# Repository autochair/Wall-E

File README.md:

View this project on [CADLAB.io](https://cadlab.io/node/973). 

# Wall-E

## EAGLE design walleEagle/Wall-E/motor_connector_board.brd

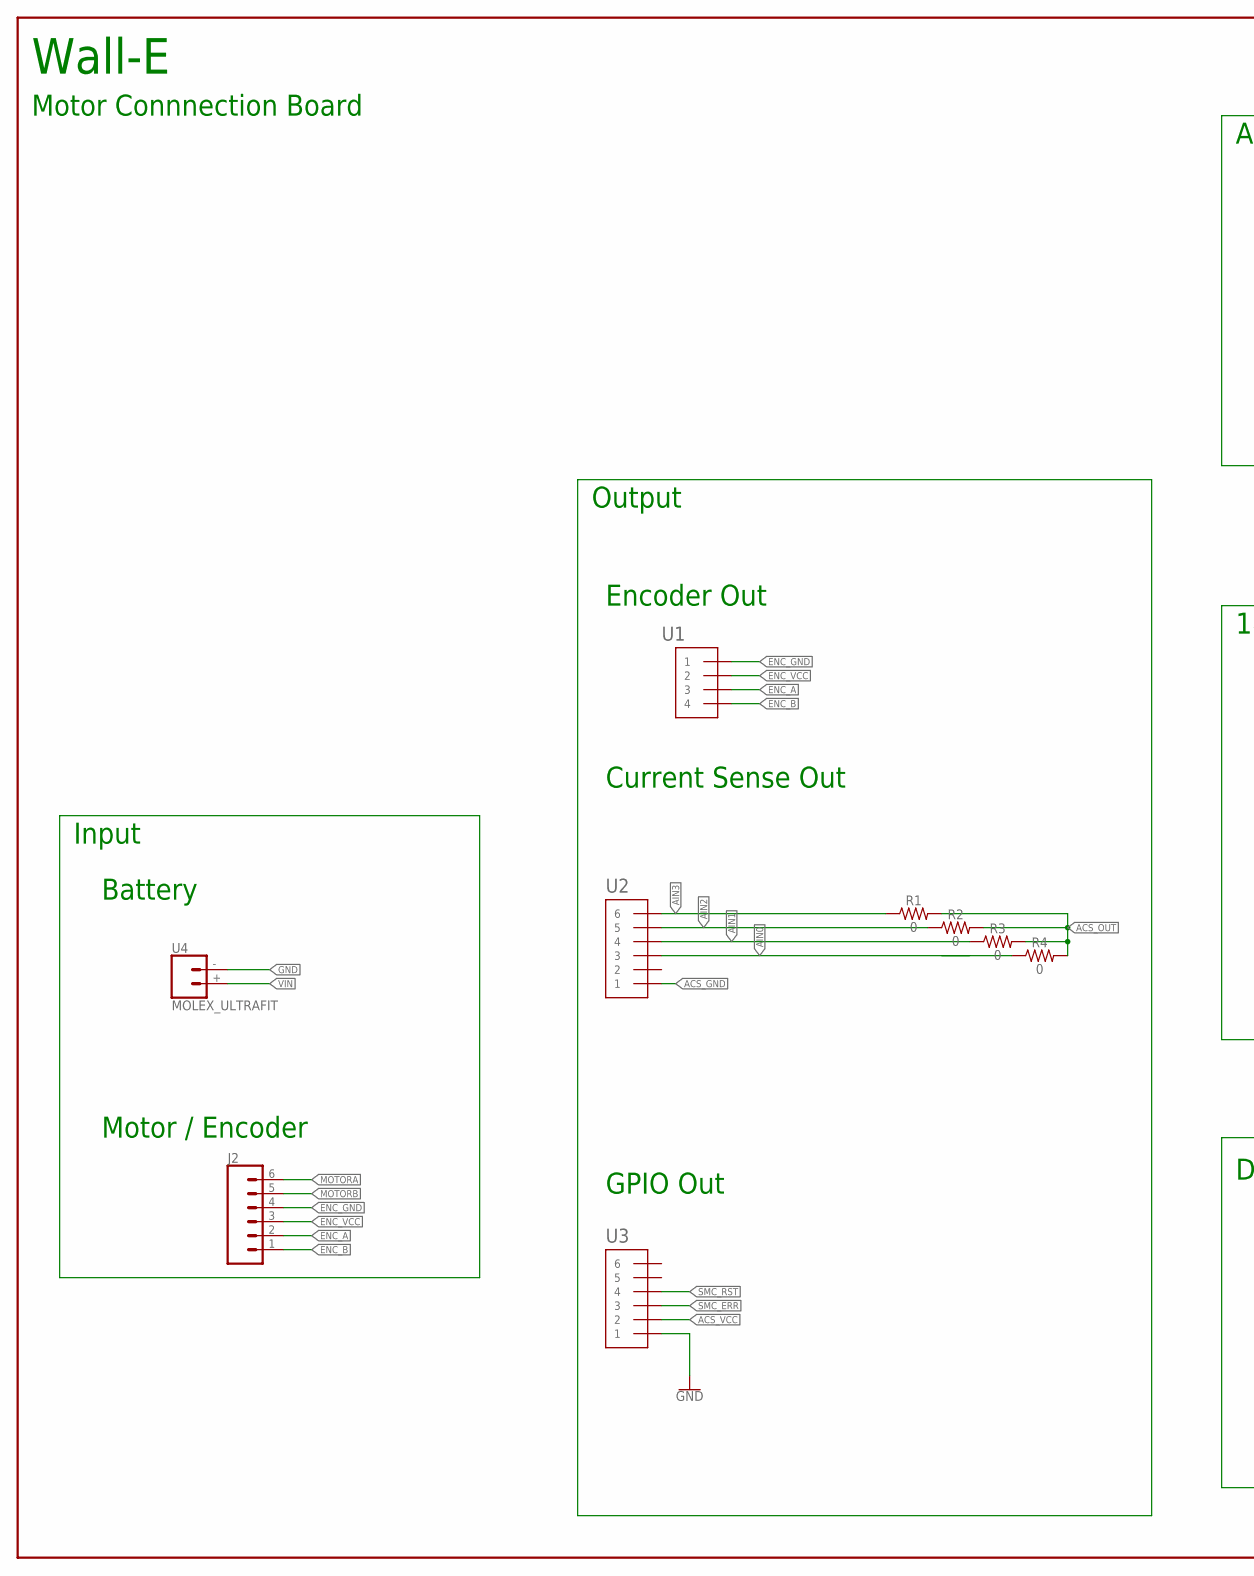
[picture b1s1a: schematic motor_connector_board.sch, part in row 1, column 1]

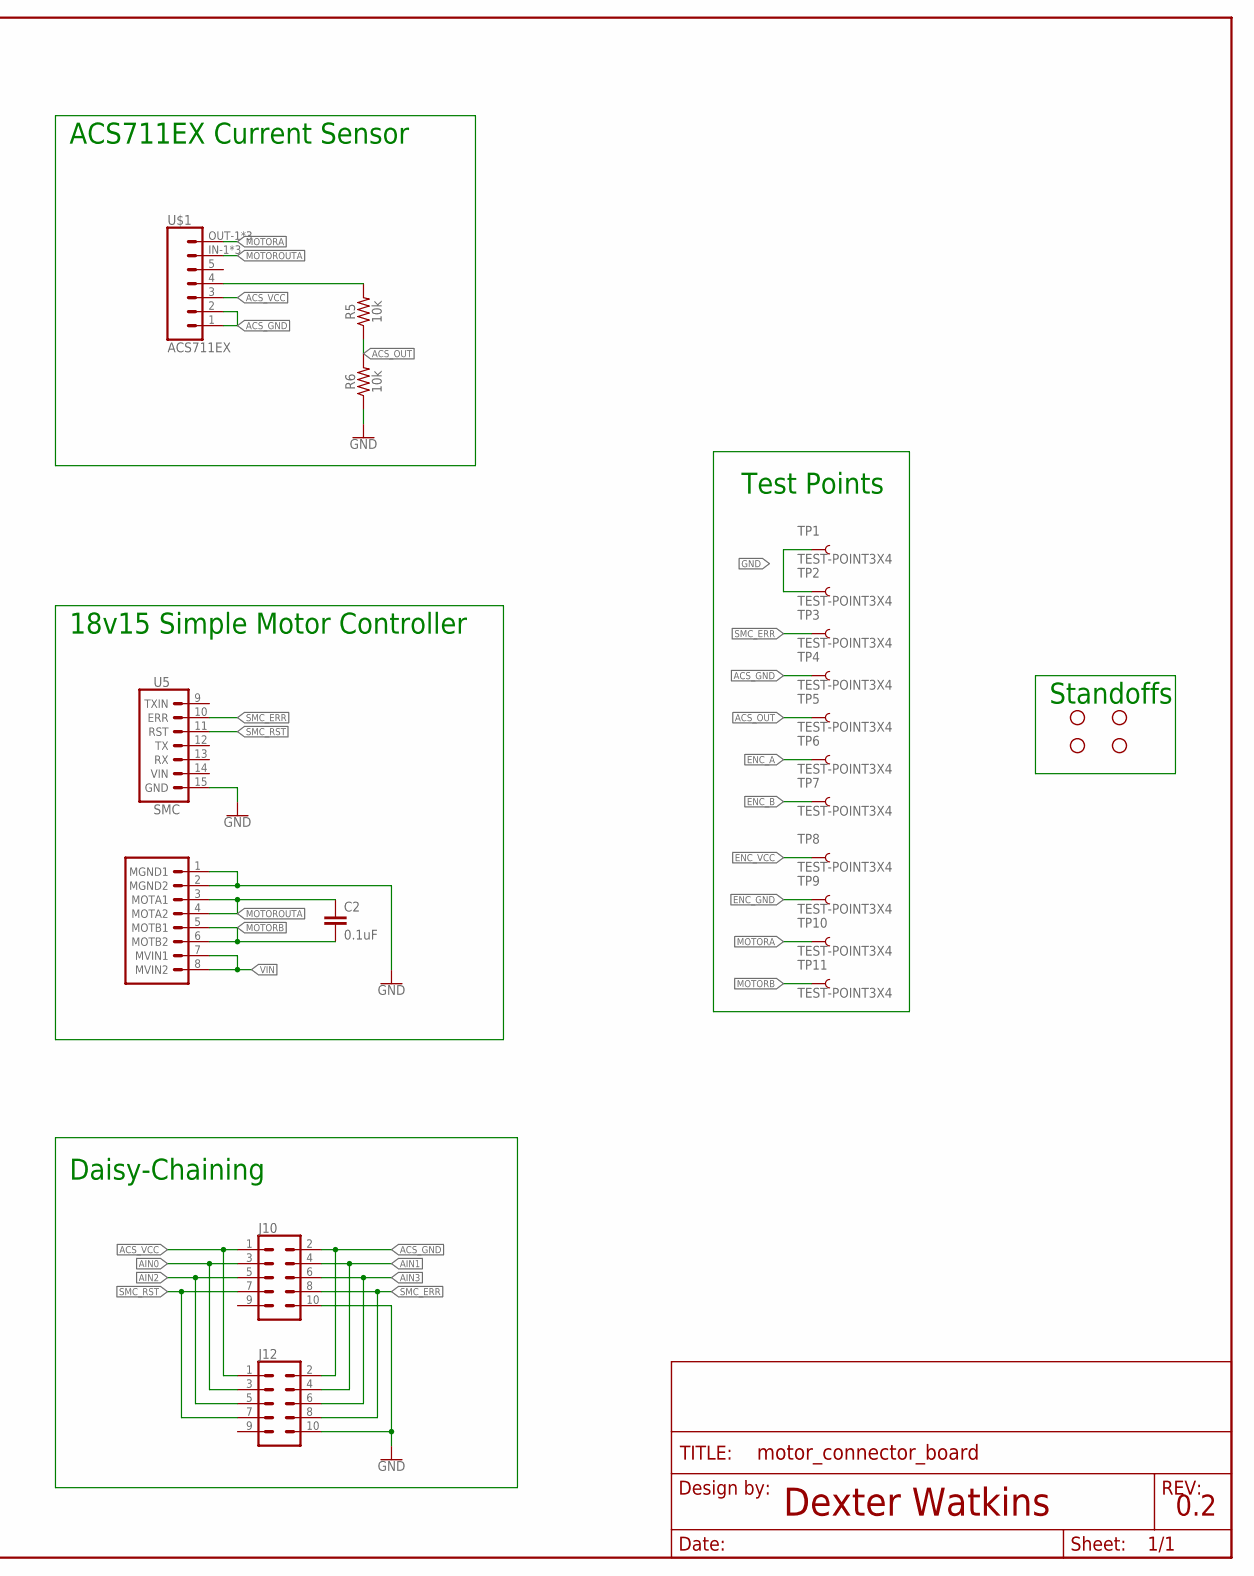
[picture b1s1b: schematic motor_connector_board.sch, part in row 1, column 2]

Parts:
C2: 0.1uF; 0603
FRAME1: FRAME-LEDGER; CREATIVE_COMMONS
H1, H2, H3, H4: STAND-OFF
J2: CONN_06LONGPADS; 1X06_LONGPADS
J10, J12: CONN_05X2SHD_LOCK; 2X5-SHROUDED_LOCK
R1, R2, R3, R4: 0; 0603
R5, R6: 10k; 0603
TP1, TP2, TP3, TP4, TP5, TP6, TP7, TP8, TP9, TP10, TP11: TEST-POINT3X4; PAD.03X.04
U1: JST_SH_4; JST_SH_4_SMD
U2, U3: JST_SH_6
U4: MOLEX_ULTRAFIT; MOLEX_ULTRAFIT-2CKT
U5: SMC
U$1: ACS711EX; ACS_CURRENT_SENSOR

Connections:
ACS_3.3OUT: R5.2, U$1.4
ACS_GND: J10.2, J12.2, TP4.P$1, U2.1, U$1.1, U$1.2
ACS_OUT: R1.2, R2.2, R3.2, R4.2, R5.1, R6.2, TP5.P$1
ACS_VCC: J10.1, J12.1, U3.2, U$1.3
AIN0: J10.3, J12.3, R4.1, U2.3
AIN1: J10.4, J12.4, R3.1, U2.4
AIN2: J10.5, J12.5, R2.1, U2.5
AIN3: J10.6, J12.6, R1.1, U2.6
ENC_A: J2.2, TP6.P$1, U1.3
ENC_B: J2.1, TP7.P$1, U1.4
ENC_GND: J2.4, TP9.P$1, U1.1
ENC_VCC: J2.3, TP8.P$1, U1.2
GND: J10.10, J12.10, R6.1, TP1.P$1, TP2.P$1, U3.1, U4.- (2), U5.1 (MGND1), U5.2 (MGND2), U5.15 (GND)
MOTORA: J2.6, TP10.P$1, U$1.OUT-1 (7), U$1.OUT-2 (7), U$1.OUT-3 (7)
MOTORB: C2.2, J2.5, TP11.P$1, U5.5 (MOTB1), U5.6 (MOTB2)
MOTOROUTA: C2.1, U5.3 (MOTA1), U5.4 (MOTA2), U$1.IN-1 (6), U$1.IN-2 (6), U$1.IN-3 (6)
SMC_ERR: J10.8, J12.8, TP3.P$1, U3.3, U5.10 (ERR)
SMC_RST: J10.7, J12.7, U3.4, U5.11 (RST)
VIN: U4.+ (1), U5.7 (MVIN1), U5.8 (MVIN2)

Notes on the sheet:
Dexter Watkins
0.2
Wall-E
Motor Connnection Board
Battery
Motor / Encoder
Encoder Out
Current Sense Out
18v15 Simple Motor Controller
ACS711EX Current Sensor
Input
Output
GPIO Out
Daisy-Chaining
Standoffs
Test Points

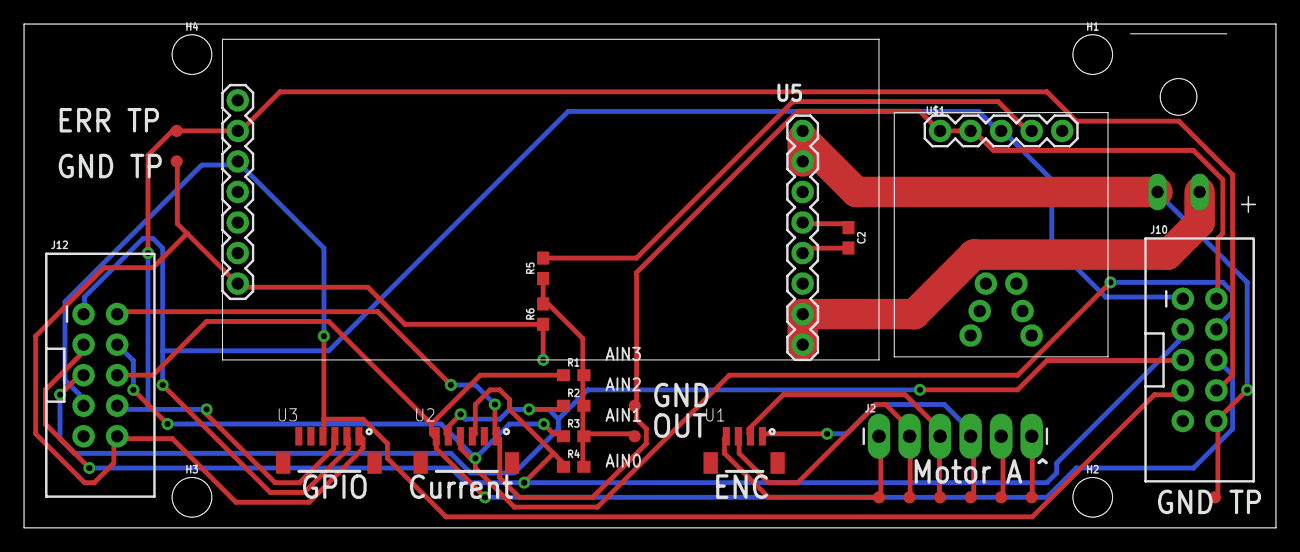
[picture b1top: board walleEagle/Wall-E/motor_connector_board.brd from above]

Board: 2 copper layers, 104.1 x 41.9 mm, 32 parts (0 on the bottom side), 19 nets.

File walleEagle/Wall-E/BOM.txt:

Partlist exported from C:/Users/dexte/Documents/repositories/Wall-E/Wall-E/motor_connector_board.sch at 12/27/2017 11:23 AM

Part   Value          Device                    Package             Description                                                                                                     PROD_ID    SF_ID     VALUE
C2     0.1uF          1.0NF/1000PF-0603-50V-10% 0603                1nF/1,000pF ceramic capacitors                                                                                  CAP-07886            1nF  
FRAME1 FRAME-LEDGER   FRAME-LEDGER              CREATIVE_COMMONS    Schematic Frame - Ledger                                                                                                                  
H1     STAND-OFF      STAND-OFF                 STAND-OFF           Stand Off                                                                                                                                 
H2     STAND-OFF      STAND-OFF                 STAND-OFF           Stand Off                                                                                                                                 
H3     STAND-OFF      STAND-OFF                 STAND-OFF           Stand Off                                                                                                                                 
H4     STAND-OFF      STAND-OFF                 STAND-OFF           Stand Off                                                                                                                                 
J2                    CONN_06LONGPADS           1X06_LONGPADS       Multi connection point. Often used as Generic Header-pin footprint for 0.1 inch spaced/style header connections                           
J10                   CONN_05X2SHD_LOCK         2X5-SHROUDED_LOCK   Multi connection point. Often used as Generic Header-pin footprint for 0.1 inch spaced/style header connections CONN-08671 PRT-08506      
J12                   CONN_05X2SHD_LOCK         2X5-SHROUDED_LOCK   Multi connection point. Often used as Generic Header-pin footprint for 0.1 inch spaced/style header connections CONN-08671 PRT-08506      
R1     0              0OHM-0603-1/10W-5%        0603                0O resistor                                                                                                     RES-08609            0    
R2     0              0OHM-0603-1/10W-5%        0603                0O resistor                                                                                                     RES-08609            0    
R3     0              0OHM-0603-1/10W-5%        0603                0O resistor                                                                                                     RES-08609            0    
R4     0              0OHM-0603-1/10W-5%        0603                0O resistor                                                                                                     RES-08609            0    
TP1    TEST-POINT3X4  TEST-POINT3X4             PAD.03X.04          SparkFun Test Points                                                                                                                      
TP2    TEST-POINT3X4  TEST-POINT3X4             PAD.03X.04          SparkFun Test Points                                                                                                                      
TP3    TEST-POINT3X4  TEST-POINT3X4             PAD.03X.04          SparkFun Test Points                                                                                                                      
TP4    TEST-POINT3X4  TEST-POINT3X4             PAD.03X.04          SparkFun Test Points                                                                                                                      
TP5    TEST-POINT3X4  TEST-POINT3X4             PAD.03X.04          SparkFun Test Points                                                                                                                      
TP6    TEST-POINT3X4  TEST-POINT3X4             PAD.03X.04          SparkFun Test Points                                                                                                                      
TP7    TEST-POINT3X4  TEST-POINT3X4             PAD.03X.04          SparkFun Test Points                                                                                                                      
TP8    TEST-POINT3X4  TEST-POINT3X4             PAD.03X.04          SparkFun Test Points                                                                                                                      
TP9    TEST-POINT3X4  TEST-POINT3X4             PAD.03X.04          SparkFun Test Points                                                                                                                      
TP10   TEST-POINT3X4  TEST-POINT3X4             PAD.03X.04          SparkFun Test Points                                                                                                                      
TP11   TEST-POINT3X4  TEST-POINT3X4             PAD.03X.04          SparkFun Test Points                                                                                                                      
U$1    ACS711EX       ACS711EX                  ACS_CURRENT_SENSOR                                                                                                                                            
U1     JST_SH_4       JST_SH_4                  JST_SH_4_SMD                                                                                                                                                  
U2     JST_SH_6       JST_SH_6                  JST_SH_6                                                                                                                                                      
U3     JST_SH_6       JST_SH_6                  JST_SH_6                                                                                                                                                      
U4     MOLEX_ULTRAFIT MOLEX_ULTRAFIT            MOLEX_ULTRAFIT-2CKT                                                                                                                                           
U5     SMC            SMC                       SMC

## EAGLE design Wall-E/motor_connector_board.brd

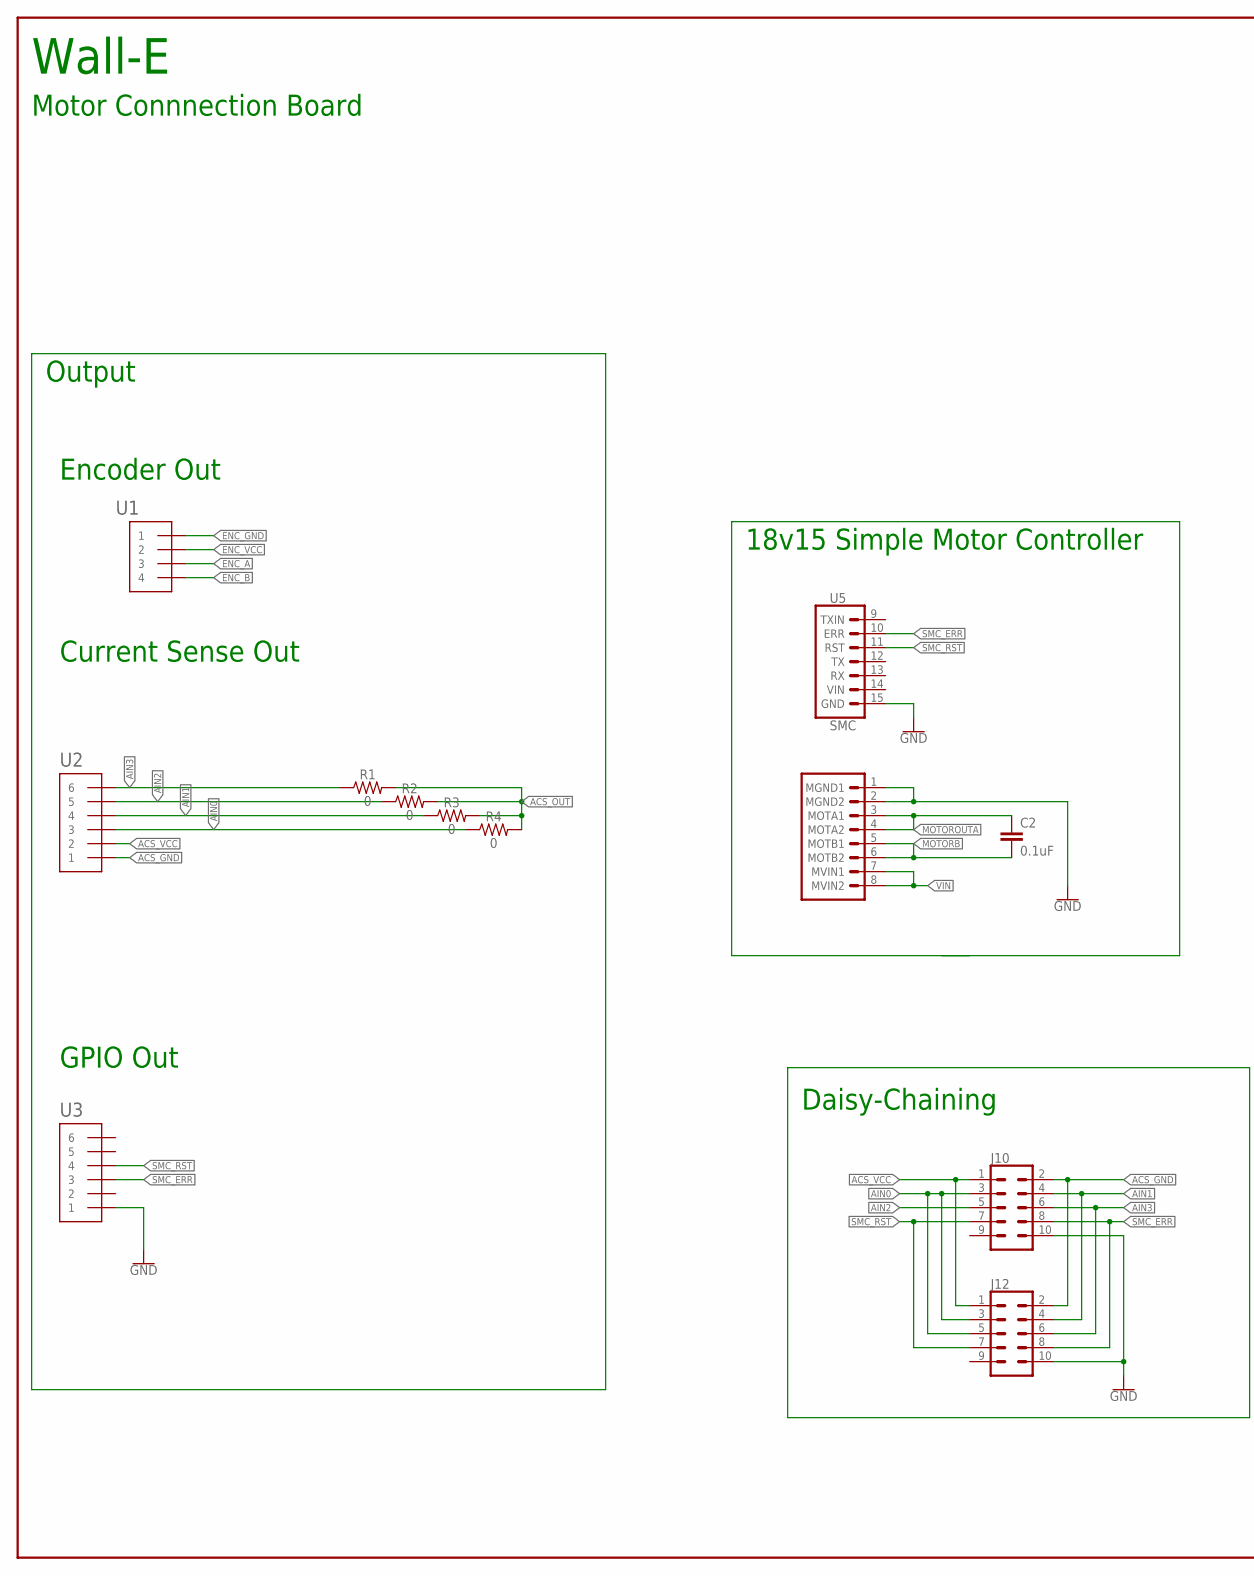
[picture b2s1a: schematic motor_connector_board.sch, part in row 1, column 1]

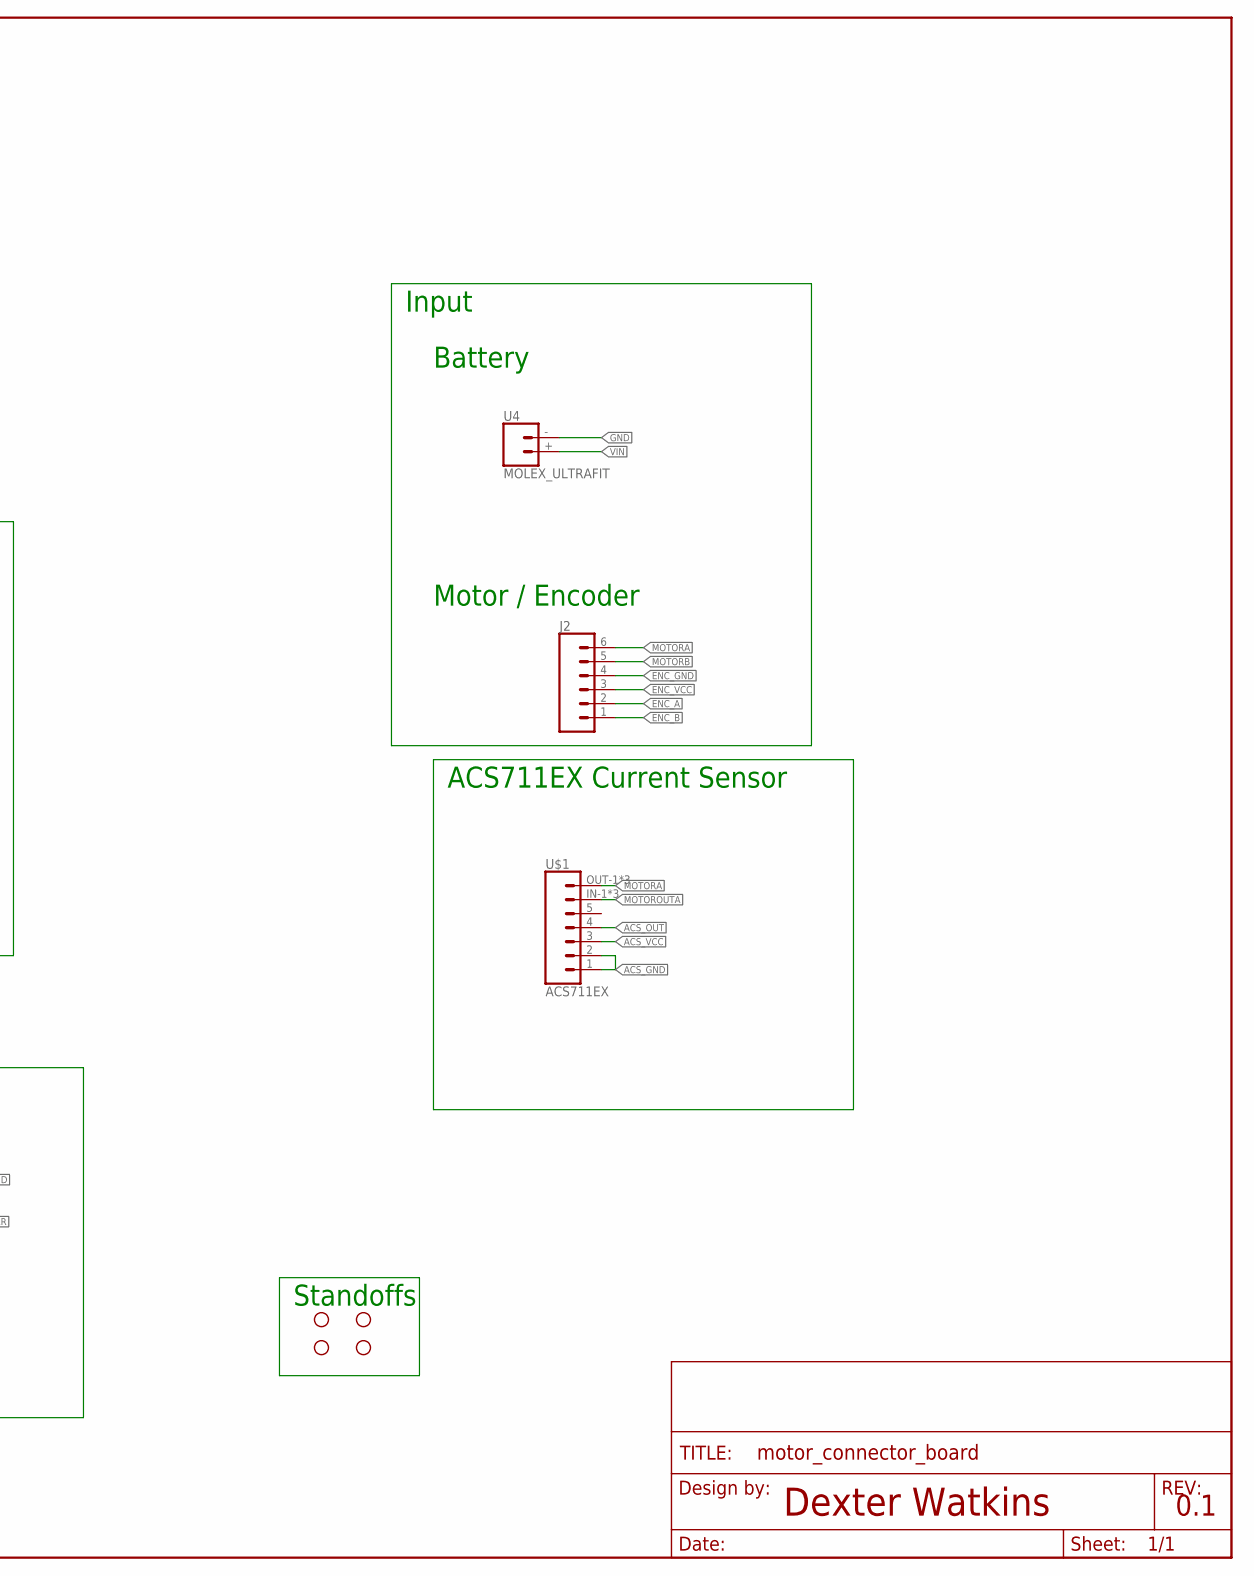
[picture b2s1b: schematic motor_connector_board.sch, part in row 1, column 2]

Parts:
C2: 0.1uF; 0603
FRAME1: FRAME-LEDGER; CREATIVE_COMMONS
H1, H2, H3, H4: STAND-OFF
J2: CONN_06LONGPADS; 1X06_LONGPADS
J10, J12: CONN_05X2SHD_LOCK; 2X5-SHROUDED_LOCK
R1, R2, R3, R4: 0; 0603
U1: JST_SH_4; JST_SH_4_SMD
U2, U3: JST_SH_6
U4: MOLEX_ULTRAFIT; MOLEX_ULTRAFIT-2CKT
U5: SMC
U$1: ACS711EX; ACS_CURRENT_SENSOR

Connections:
ACS_GND: J10.2, J12.2, U2.1, U$1.1, U$1.2
ACS_OUT: R1.2, R2.2, R3.2, R4.2, U$1.4
ACS_VCC: J10.1, J12.1, U2.2, U$1.3
AIN0: J10.3, J12.3, J12.5, R4.1, U2.3
AIN1: J10.4, J12.4, R3.1, U2.4
AIN2: J10.5, R2.1, U2.5
AIN3: J10.6, J12.6, R1.1, U2.6
ENC_A: J2.2, U1.3
ENC_B: J2.1, U1.4
ENC_GND: J2.4, U1.1
ENC_VCC: J2.3, U1.2
GND: J10.10, J12.10, U3.1, U4.- (2), U5.1 (MGND1), U5.2 (MGND2), U5.15 (GND)
MOTORA: J2.6, U$1.OUT-1 (7), U$1.OUT-2 (7), U$1.OUT-3 (7)
MOTORB: C2.2, J2.5, U5.5 (MOTB1), U5.6 (MOTB2)
MOTOROUTA: C2.1, U5.3 (MOTA1), U5.4 (MOTA2), U$1.IN-1 (6), U$1.IN-2 (6), U$1.IN-3 (6)
SMC_ERR: J10.8, J12.8, U3.3, U5.10 (ERR)
SMC_RST: J10.7, J12.7, U3.4, U5.11 (RST)
VIN: U4.+ (1), U5.7 (MVIN1), U5.8 (MVIN2)

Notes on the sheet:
Dexter Watkins
0.1
Wall-E
Motor Connnection Board
Battery
Motor / Encoder
Encoder Out
Current Sense Out
18v15 Simple Motor Controller
ACS711EX Current Sensor
Input
Output
GPIO Out
Daisy-Chaining
Standoffs

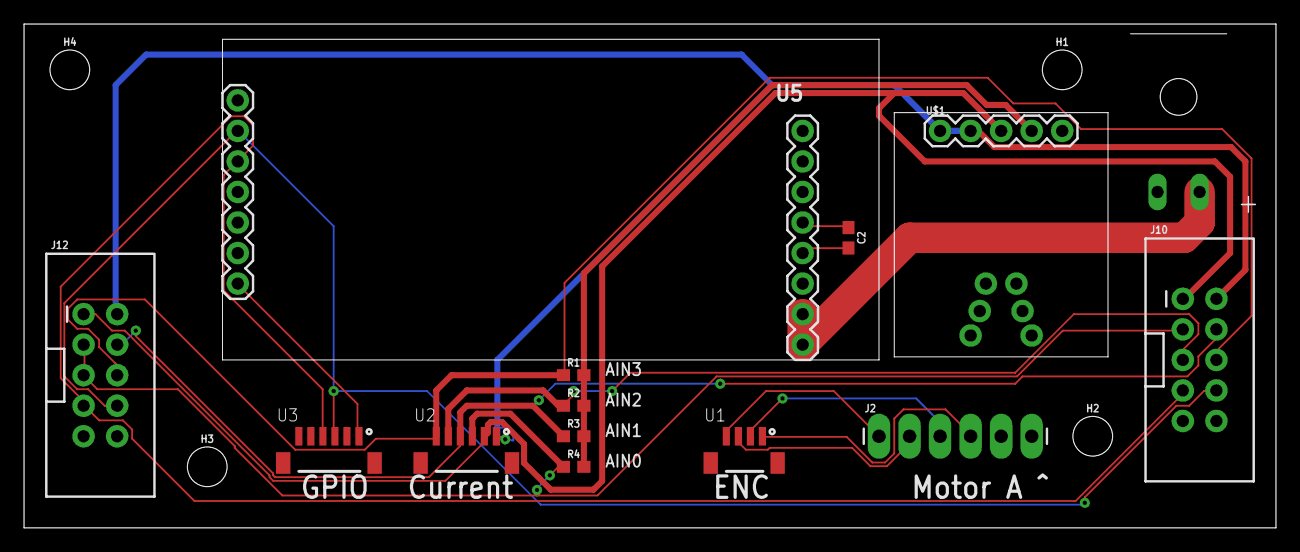
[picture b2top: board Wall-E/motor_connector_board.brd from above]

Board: 2 copper layers, 104.1 x 41.9 mm, 19 parts (0 on the bottom side), 18 nets.

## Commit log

2017-12-21 started motor board pcb
2017-12-22 continued pcb
2017-12-27 completed first motor pcb
2018-01-08 fixed error on ribbon cable connector
2018-01-09 added voltage divider for current sense, rerouted current sense power to a 3.3 line, and minor tweaks to routing
2018-01-09 added reset test, learned I need to export err pin too
2018-01-19 added initial cad
2018-01-19 changed eagle directory
2018-01-19 removed temp files
2018-01-23 added rosmod model backup
2018-01-23 updated rosmod model
2018-01-29 completely redid routing and made standoffs symmetrical
2018-05-03 Backlink to CADLAB.io has been added.

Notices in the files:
parts and their libraries:
SparkFun-Connectors: Licensing: Creative Commons ShareAlike 4.0 International - https://creativecommons.org/licenses/by-sa/4.0
